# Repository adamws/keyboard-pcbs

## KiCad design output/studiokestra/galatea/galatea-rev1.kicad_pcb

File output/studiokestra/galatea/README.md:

## studiokestra/galatea/galatea-rev1

[layout](galatea-rev1-kle.json) - [PCB](galatea-rev1.kicad_pcb)

{:loading="lazy"}

[Open in keyboard-layout-editor](http://www.keyboard-layout-editor.com/##@@_x:2.5&y:1.25&c=#777777;&=0,0&_x:0.25&c=#cccccc;&=1,0%0A%0A%0A0,0&=0,1%0A%0A%0A0,0&=0,2%0A%0A%0A0,0&=1,2%0A%0A%0A0,0&_x:0.25&c=#aaaaaa;&=0,3%0A%0A%0A0,0&=1,3%0A%0A%0A0,0&=0,4%0A%0A%0A0,0&=1,4%0A%0A%0A0,0&_x:0.25&c=#cccccc;&=0,5%0A%0A%0A0,0&=1,5%0A%0A%0A0,0&=0,6%0A%0A%0A0,0&=1,6%0A%0A%0A0,0&_x:0.25&c=#aaaaaa;&=0,7%0A%0A%0A0,0&_x:0.25&c=#cccccc;&=1,7&=0,8&=1,8;&@_x:2.5&y:0.25&c=#aaaaaa;&=2,0&_c=#cccccc;&=3,0&=2,1&=3,1&=2,2&=3,2&=2,3&=3,3&=2,4&=3,4&=2,5&=3,5&=2,6&_c=#aaaaaa&w:2;&=3,6%0A%0A%0A1,0&_x:0.25&c=#cccccc;&=3,7&=2,8&=3,8;&@_x:2.5&c=#aaaaaa&w:1.5;&=4,0&_c=#cccccc;&=5,0&=4,1&=5,1&=4,2&=5,2&=4,3&=5,3&=4,4&=5,4&=4,5&=5,5&=4,6&_w:1.5;&=4,7%0A%0A%0A2,0&_x:0.25;&=5,7&=4,8&=5,8;&@_x:2.5&c=#aaaaaa&w:1.75;&=6,0&_c=#cccccc;&=7,0&=6,1&=7,1&=6,2&=7,2&=6,3&=7,3&=6,4&=7,4&=6,5&=7,5&_c=#777777&w:2.25;&=6,6%0A%0A%0A2,0;&@_x:2.5&c=#aaaaaa&w:2.25;&=8,0%0A%0A%0A3,0&_c=#cccccc;&=8,1&=9,1&=8,2&=9,2&=8,3&=9,3&=8,4&=9,4&=8,5&=9,5&_c=#aaaaaa&w:2.75;&=8,6%0A%0A%0A4,0&_x:1.25&c=#cccccc;&=8,8;&@_x:2.5&c=#aaaaaa&w:1.25;&=10,0%0A%0A%0A5,0&_w:1.25;&=11,0%0A%0A%0A5,0&_w:1.25;&=10,1%0A%0A%0A5,0&_c=#cccccc&w:6.25;&=10,3%0A%0A%0A5,0&_c=#aaaaaa&w:1.25;&=10,5%0A%0A%0A5,0&_w:1.25;&=11,5%0A%0A%0A5,0&_w:1.25;&=10,6%0A%0A%0A5,0&_w:1.25;&=10,7%0A%0A%0A5,0&_x:0.25&c=#cccccc;&=11,7&=10,8&=11,8;&@_x:3.75&y:-7.5&d:true;&=1,0%0A%0A%0A0,1&_x:-0.25;&=0,1%0A%0A%0A0,1&=0,2%0A%0A%0A0,1&=1,2%0A%0A%0A0,1&=0,3%0A%0A%0A0,1&_x:0.5&c=#aaaaaa;&=1,3%0A%0A%0A0,1&=0,4%0A%0A%0A0,1&=1,4%0A%0A%0A0,1&=0,5%0A%0A%0A0,1&_x:0.5&c=#cccccc;&=1,5%0A%0A%0A0,1&=0,6%0A%0A%0A0,1&=1,6%0A%0A%0A0,1&=0,7%0A%0A%0A0,1;&@_x:21.75&y:1.5;&=3,6%0A%0A%0A1,1&=2,7%0A%0A%0A1,1;&@_x:22.5&c=#777777&w:1.25&h:2&w2:1.5&h2:1&x2:-0.25;&=4,7%0A%0A%0A2,1;&@_x:21.5&c=#cccccc;&=6,6%0A%0A%0A2,1;&@_c=#aaaaaa&w:1.25;&=8,0%0A%0A%0A3,1&=9,0%0A%0A%0A3,1&_x:18.75&w:1.75;&=8,6%0A%0A%0A4,1&=8,7%0A%0A%0A4,1;&@_x:2.5&y:1.25&w:1.5;&=10,0%0A%0A%0A5,1&=11,0%0A%0A%0A5,1&_w:1.5;&=10,1%0A%0A%0A5,1&_c=#cccccc&w:7;&=10,3%0A%0A%0A5,1&_c=#aaaaaa&w:1.5;&=11,5%0A%0A%0A5,1&=10,6%0A%0A%0A5,1&_w:1.5;&=10,7%0A%0A%0A5,1;&@_x:2.5&w:1.5;&=10,0%0A%0A%0A5,2&_c=#cccccc&d:true;&=11,0%0A%0A%0A5,2&_c=#aaaaaa&w:1.5;&=10,1%0A%0A%0A5,2&_c=#cccccc&w:7;&=10,3%0A%0A%0A5,2&_c=#aaaaaa&w:1.5;&=11,5%0A%0A%0A5,2&_c=#cccccc&d:true;&=10,6%0A%0A%0A5,2&_c=#aaaaaa&w:1.5;&=10,7%0A%0A%0A5,2;&@_x:2.5&w:1.25;&=10,0%0A%0A%0A5,3&_w:1.25;&=11,0%0A%0A%0A5,3&_c=#cccccc&w:10;&=10,3%0A%0A%0A5,3&_c=#aaaaaa&w:1.25;&=10,6%0A%0A%0A5,3&_w:1.25;&=10,7%0A%0A%0A5,3;&@_x:2.5&w:1.5;&=10,0%0A%0A%0A5,4&_c=#cccccc&d:true;&=11,0%0A%0A%0A5,4&_w:10;&=10,3%0A%0A%0A5,4&_d:true;&=10,6%0A%0A%0A5,4&_c=#aaaaaa&w:1.5;&=10,7%0A%0A%0A5,4)

{:loading="lazy"}

## studiokestra/galatea/galatea-rev2

[layout](galatea-rev2-kle.json) - [PCB](galatea-rev2.kicad_pcb)

{:loading="lazy"}

[Open in keyboard-layout-editor](http://www.keyboard-layout-editor.com/##@@_x:2.5&y:1.25&c=#777777;&=0,0&_x:0.25&c=#cccccc;&=1,0%0A%0A%0A0,0&=0,1%0A%0A%0A0,0&=0,2%0A%0A%0A0,0&=1,2%0A%0A%0A0,0&_x:0.25&c=#aaaaaa;&=0,3%0A%0A%0A0,0&=1,3%0A%0A%0A0,0&=0,4%0A%0A%0A0,0&=1,4%0A%0A%0A0,0&_x:0.25&c=#cccccc;&=0,5%0A%0A%0A0,0&=1,5%0A%0A%0A0,0&=0,6%0A%0A%0A0,0&=1,6%0A%0A%0A0,0&_x:0.25&c=#aaaaaa;&=0,7%0A%0A%0A0,0&_x:0.25&c=#cccccc;&=1,7&=0,8&=1,8;&@_x:2.5&y:0.25&c=#aaaaaa;&=2,0&_c=#cccccc;&=3,0&=2,1&=3,1&=2,2&=3,2&=2,3&=3,3&=2,4&=3,4&=2,5&=3,5&=2,6&_c=#aaaaaa&w:2;&=3,6%0A%0A%0A1,0&_x:0.25&c=#cccccc;&=3,7&=2,8&=3,8;&@_x:2.5&c=#aaaaaa&w:1.5;&=4,0&_c=#cccccc;&=5,0&=4,1&=5,1&=4,2&=5,2&=4,3&=5,3&=4,4&=5,4&=4,5&=5,5&=4,6&_w:1.5;&=4,7%0A%0A%0A2,0&_x:0.25;&=5,7&=4,8&=5,8;&@_x:2.5&c=#aaaaaa&w:1.75;&=6,0&_c=#cccccc;&=7,0&=6,1&=7,1&=6,2&=7,2&=6,3&=7,3&=6,4&=7,4&=6,5&=7,5&_c=#777777&w:2.25;&=6,6%0A%0A%0A2,0;&@_x:2.5&c=#aaaaaa&w:2.25;&=8,0%0A%0A%0A3,0&_c=#cccccc;&=8,1&=9,1&=8,2&=9,2&=8,3&=9,3&=8,4&=9,4&=8,5&=9,5&_c=#aaaaaa&w:2.75;&=8,6%0A%0A%0A4,0&_x:1.25&c=#cccccc;&=8,8;&@_x:2.5&c=#aaaaaa&w:1.25;&=10,0%0A%0A%0A5,0&_w:1.25;&=11,0%0A%0A%0A5,0&_w:1.25;&=10,1%0A%0A%0A5,0&_c=#cccccc&w:6.25;&=10,3%0A%0A%0A5,0&_c=#aaaaaa&w:1.25;&=10,5%0A%0A%0A5,0&_w:1.25;&=11,5%0A%0A%0A5,0&_w:1.25;&=10,6%0A%0A%0A5,0&_w:1.25;&=10,7%0A%0A%0A5,0&_x:0.25&c=#cccccc;&=11,7&=10,8&=11,8;&@_x:3.75&y:-7.5&d:true;&=1,0%0A%0A%0A0,1&_x:-0.25;&=0,1%0A%0A%0A0,1&=0,2%0A%0A%0A0,1&=1,2%0A%0A%0A0,1&=0,3%0A%0A%0A0,1&_x:0.5&c=#aaaaaa;&=1,3%0A%0A%0A0,1&=0,4%0A%0A%0A0,1&=1,4%0A%0A%0A0,1&=0,5%0A%0A%0A0,1&_x:0.5&c=#cccccc;&=1,5%0A%0A%0A0,1&=0,6%0A%0A%0A0,1&=1,6%0A%0A%0A0,1&=0,7%0A%0A%0A0,1;&@_x:21.75&y:1.5;&=3,6%0A%0A%0A1,1&=2,7%0A%0A%0A1,1;&@_x:22.5&c=#777777&w:1.25&h:2&w2:1.5&h2:1&x2:-0.25;&=4,7%0A%0A%0A2,1;&@_x:21.5&c=#cccccc;&=6,6%0A%0A%0A2,1;&@_c=#aaaaaa&w:1.25;&=8,0%0A%0A%0A3,1&=9,0%0A%0A%0A3,1&_x:18.75&w:1.75;&=8,6%0A%0A%0A4,1&=8,7%0A%0A%0A4,1;&@_x:2.5&y:1.25&w:1.5;&=10,0%0A%0A%0A5,1&=11,0%0A%0A%0A5,1&_w:1.5;&=10,1%0A%0A%0A5,1&_c=#cccccc&w:7;&=10,3%0A%0A%0A5,1&_c=#aaaaaa&w:1.5;&=11,5%0A%0A%0A5,1&=10,6%0A%0A%0A5,1&_w:1.5;&=10,7%0A%0A%0A5,1;&@_x:2.5&w:1.5;&=10,0%0A%0A%0A5,2&_c=#cccccc&d:true;&=11,0%0A%0A%0A5,2&_c=#aaaaaa&w:1.5;&=10,1%0A%0A%0A5,2&_c=#cccccc&w:7;&=10,3%0A%0A%0A5,2&_c=#aaaaaa&w:1.5;&=11,5%0A%0A%0A5,2&_c=#cccccc&d:true;&=10,6%0A%0A%0A5,2&_c=#aaaaaa&w:1.5;&=10,7%0A%0A%0A5,2;&@_x:2.5&w:1.25;&=10,0%0A%0A%0A5,3&_w:1.25;&=11,0%0A%0A%0A5,3&_c=#cccccc&w:10;&=10,3%0A%0A%0A5,3&_c=#aaaaaa&w:1.25;&=10,6%0A%0A%0A5,3&_w:1.25;&=10,7%0A%0A%0A5,3;&@_x:2.5&w:1.5;&=10,0%0A%0A%0A5,4&_c=#cccccc&d:true;&=11,0%0A%0A%0A5,4&_w:10;&=10,3%0A%0A%0A5,4&_d:true;&=10,6%0A%0A%0A5,4&_c=#aaaaaa&w:1.5;&=10,7%0A%0A%0A5,4)

{:loading="lazy"}

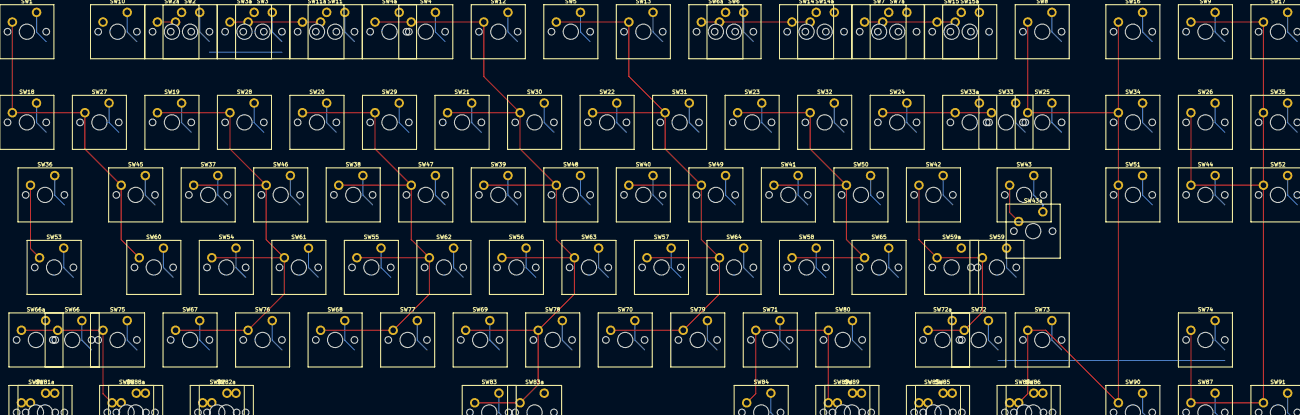
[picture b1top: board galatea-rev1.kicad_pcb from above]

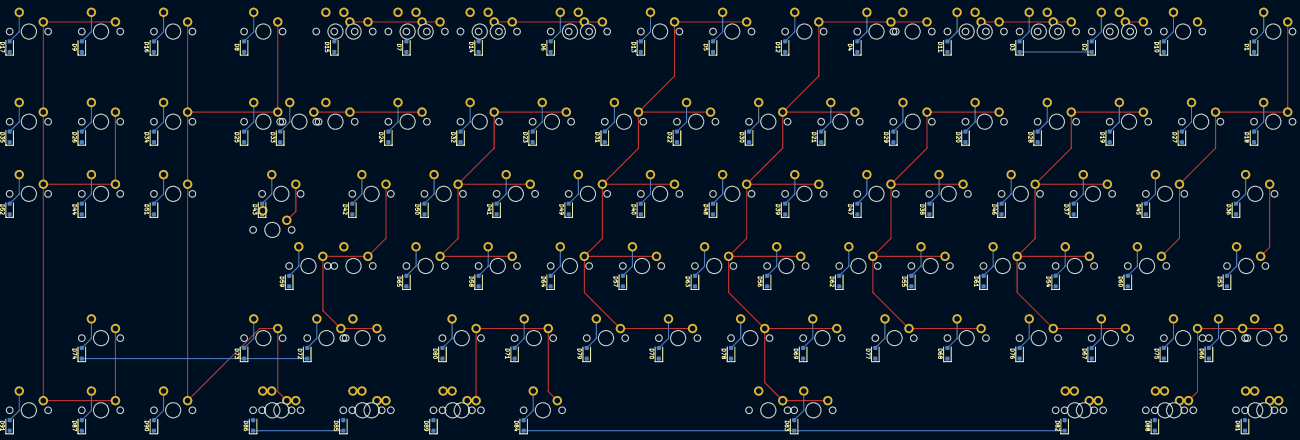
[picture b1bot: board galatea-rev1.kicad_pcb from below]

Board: 2 copper layers, 202 parts (91 on the bottom side), 112 nets.

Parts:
D1, D2, D3, D4, D5, D6, D7, D8, D9, D10, D11, D12, D13, D14, D15, D16, D17, D18, D19, D20, D21, D22, D23, D24, D25, D26, D27, D28, D29, D30, D31, D32, D33, D34, D35, D36, D37, D38, D39, D40, D41, D42, D43, D44, D45, D46, D47, D48, D49, D50, D51, D52, D53, D54, D55, D56, D57, D58, D59, D60, D61, D62, D63, D64, D65, D66, D67, D68, D69, D70, D71, D72, D73, D74, D75, D76, D77, D78, D79, D80, D81, D82, D83, D84, D85, D86, D87, D88, D89, D90, D91: D_SOD-123F
SW1, SW2, SW2a, SW3, SW3a, SW4, SW4a, SW5, SW6, SW6a, SW7, SW7a, SW8, SW9, SW10, SW11, SW11a, SW12, SW13, SW14, SW14a, SW15, SW15a, SW16, SW17, SW18, SW19, SW20, SW21, SW22, SW23, SW24, SW25, SW26, SW27, SW28, SW29, SW30, SW31, SW32, SW33, SW33a, SW34, SW35, SW36, SW37, SW38, SW39, SW40, SW41, SW42, SW43, SW43a, SW44, SW45, SW46, SW47, SW48, SW49, SW50, SW51, SW52, SW53, SW54, SW55, SW56, SW57, SW58, SW59, SW59a, SW60, SW61, SW62, SW63, SW64, SW65, SW66, SW66a, SW67, SW68, SW69, SW70, SW71, SW72, SW72a, SW73, SW74, SW75, SW76, SW77, SW78, SW79, SW80, SW81, SW81a, SW82, SW82a, SW83, SW83a, SW84, SW85, SW85a, SW86, SW86a, SW87, SW88, SW88a, SW89, SW89a, SW90, SW91: SW_Cherry_MX_PCB_1.00u

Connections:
COL0: SW1.1, SW10.1, SW18.1, SW27.1, SW36.1, SW45.1, SW53.1, SW60.1, SW66.1, SW66a.1, SW75.1, SW81.1, SW81a.1, SW88.1, SW88a.1
COL1: SW2.1, SW2a.1, SW19.1, SW28.1, SW37.1, SW46.1, SW54.1, SW61.1, SW67.1, SW76.1, SW82.1, SW82a.1
COL2: SW3.1, SW3a.1, SW11.1, SW11a.1, SW20.1, SW29.1, SW38.1, SW47.1, SW55.1, SW62.1, SW68.1, SW77.1
COL3: SW4.1, SW4a.1, SW12.1, SW21.1, SW30.1, SW39.1, SW48.1, SW56.1, SW63.1, SW69.1, SW78.1, SW83.1, SW83a.1
COL4: SW5.1, SW13.1, SW22.1, SW31.1, SW40.1, SW49.1, SW57.1, SW64.1, SW70.1, SW79.1
COL5: SW6.1, SW6a.1, SW14.1, SW14a.1, SW23.1, SW32.1, SW41.1, SW50.1, SW58.1, SW65.1, SW71.1, SW80.1, SW84.1, SW89.1, SW89a.1
COL6: SW7.1, SW7a.1, SW15.1, SW15a.1, SW24.1, SW33.1, SW33a.1, SW42.1, SW59.1, SW59a.1, SW72.1, SW72a.1, SW85.1, SW85a.1
COL7: SW8.1, SW16.1, SW25.1, SW34.1, SW43.1, SW43a.1, SW51.1, SW73.1, SW86.1, SW86a.1, SW90.1
COL8: SW9.1, SW17.1, SW26.1, SW35.1, SW44.1, SW52.1, SW74.1, SW87.1, SW91.1
unnamed: D1.2, SW1.2
unnamed: D2.2, SW2.2, SW2a.2
unnamed: D3.2, SW3.2, SW3a.2
unnamed: D4.2, SW4.2, SW4a.2
unnamed: D5.2, SW5.2
unnamed: D6.2, SW6.2, SW6a.2
unnamed: D7.2, SW7.2, SW7a.2
unnamed: D8.2, SW8.2
unnamed: D9.2, SW9.2
unnamed: D10.2, SW10.2
unnamed: D11.2, SW11.2, SW11a.2
unnamed: D12.2, SW12.2
unnamed: D13.2, SW13.2
unnamed: D14.2, SW14.2, SW14a.2
unnamed: D15.2, SW15.2, SW15a.2
unnamed: D16.2, SW16.2
unnamed: D17.2, SW17.2
unnamed: D18.2, SW18.2
unnamed: D19.2, SW19.2
unnamed: D20.2, SW20.2
unnamed: D21.2, SW21.2
unnamed: D22.2, SW22.2
unnamed: D23.2, SW23.2
unnamed: D24.2, SW24.2
unnamed: D25.2, SW25.2
unnamed: D26.2, SW26.2
unnamed: D27.2, SW27.2
unnamed: D28.2, SW28.2
unnamed: D29.2, SW29.2
unnamed: D30.2, SW30.2
unnamed: D31.2, SW31.2
unnamed: D32.2, SW32.2
unnamed: D33.2, SW33.2, SW33a.2
unnamed: D34.2, SW34.2
unnamed: D35.2, SW35.2
unnamed: D36.2, SW36.2
unnamed: D37.2, SW37.2
unnamed: D38.2, SW38.2
unnamed: D39.2, SW39.2
unnamed: D40.2, SW40.2
unnamed: D41.2, SW41.2
unnamed: D42.2, SW42.2
unnamed: D43.2, SW43.2, SW43a.2
unnamed: D44.2, SW44.2
unnamed: D45.2, SW45.2
unnamed: D46.2, SW46.2
unnamed: D47.2, SW47.2
unnamed: D48.2, SW48.2
unnamed: D49.2, SW49.2
unnamed: D50.2, SW50.2
unnamed: D51.2, SW51.2
unnamed: D52.2, SW52.2
unnamed: D53.2, SW53.2
unnamed: D54.2, SW54.2
unnamed: D55.2, SW55.2
unnamed: D56.2, SW56.2
unnamed: D57.2, SW57.2
unnamed: D58.2, SW58.2
unnamed: D59.2, SW59.2, SW59a.2
unnamed: D60.2, SW60.2
unnamed: D61.2, SW61.2
unnamed: D62.2, SW62.2
unnamed: D63.2, SW63.2
unnamed: D64.2, SW64.2
unnamed: D65.2, SW65.2
unnamed: D66.2, SW66.2, SW66a.2
unnamed: D67.2, SW67.2
unnamed: D68.2, SW68.2
unnamed: D69.2, SW69.2
unnamed: D70.2, SW70.2
unnamed: D71.2, SW71.2
unnamed: D72.2, SW72.2, SW72a.2
unnamed: D73.2, SW73.2
unnamed: D74.2, SW74.2
unnamed: D75.2, SW75.2
unnamed: D76.2, SW76.2
unnamed: D77.2, SW77.2
unnamed: D78.2, SW78.2
unnamed: D79.2, SW79.2
unnamed: D80.2, SW80.2
unnamed: D81.2, SW81.2, SW81a.2
unnamed: D82.2, SW82.2, SW82a.2
unnamed: D83.2, SW83.2, SW83a.2
unnamed: D84.2, SW84.2
unnamed: D85.2, SW85.2, SW85a.2
unnamed: D86.2, SW86.2, SW86a.2
unnamed: D87.2, SW87.2
unnamed: D88.2, SW88.2, SW88a.2
unnamed: D89.2, SW89.2, SW89a.2
unnamed: D90.2, SW90.2
unnamed: D91.2, SW91.2
ROW0: D1.1, D2.1, D3.1, D4.1, D5.1, D6.1, D7.1, D8.1, D9.1
ROW1: D10.1, D11.1, D12.1, D13.1, D14.1, D15.1, D16.1, D17.1
ROW2: D18.1, D19.1, D20.1, D21.1, D22.1, D23.1, D24.1, D25.1, D26.1
ROW3: D27.1, D28.1, D29.1, D30.1, D31.1, D32.1, D33.1, D34.1, D35.1
ROW4: D36.1, D37.1, D38.1, D39.1, D40.1, D41.1, D42.1, D43.1, D44.1
ROW5: D45.1, D46.1, D47.1, D48.1, D49.1, D50.1, D51.1, D52.1
ROW6: D53.1, D54.1, D55.1, D56.1, D57.1, D58.1, D59.1
ROW7: D60.1, D61.1, D62.1, D63.1, D64.1, D65.1
ROW8: D66.1, D67.1, D68.1, D69.1, D70.1, D71.1, D72.1, D73.1, D74.1
ROW9: D75.1, D76.1, D77.1, D78.1, D79.1, D80.1
ROW10: D81.1, D82.1, D83.1, D84.1, D85.1, D86.1, D87.1
ROW11: D88.1, D89.1, D90.1, D91.1

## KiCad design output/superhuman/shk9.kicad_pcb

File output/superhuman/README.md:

## superhuman/shk9

[layout](shk9-kle.json) - [PCB](shk9.kicad_pcb)

{:loading="lazy"}

[Open in keyboard-layout-editor](http://www.keyboard-layout-editor.com/##@@=0,0&=0,1&=0,2;&@=1,0&=1,1&=1,2;&@=2,0&=2,1&=2,2)

{:loading="lazy"}

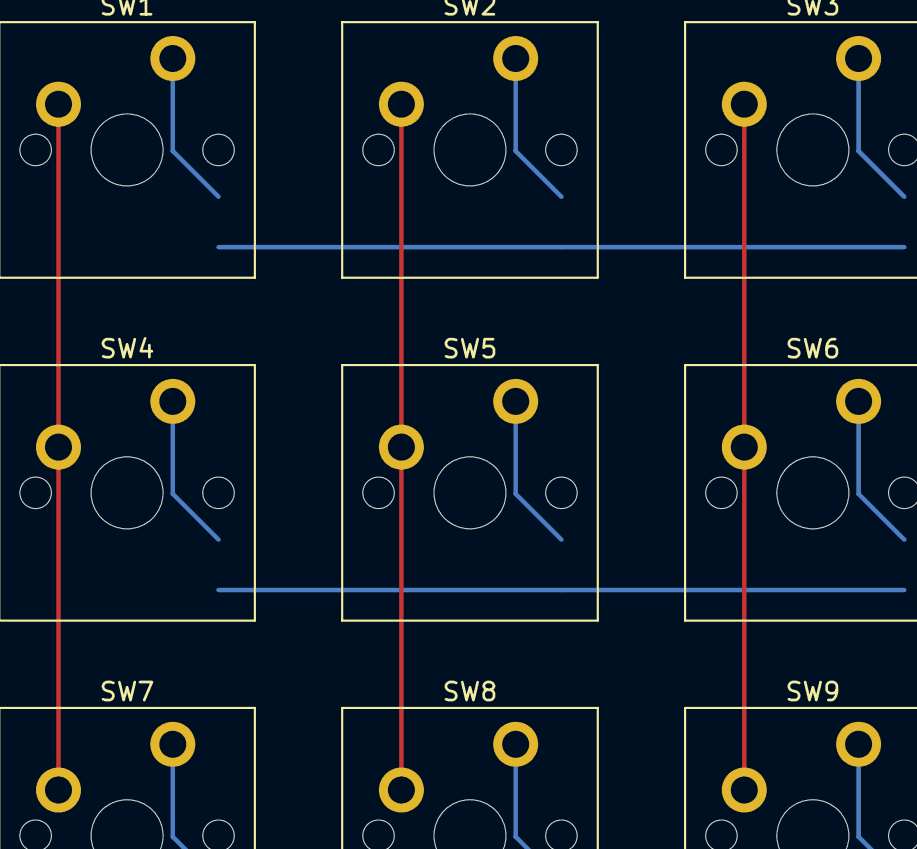
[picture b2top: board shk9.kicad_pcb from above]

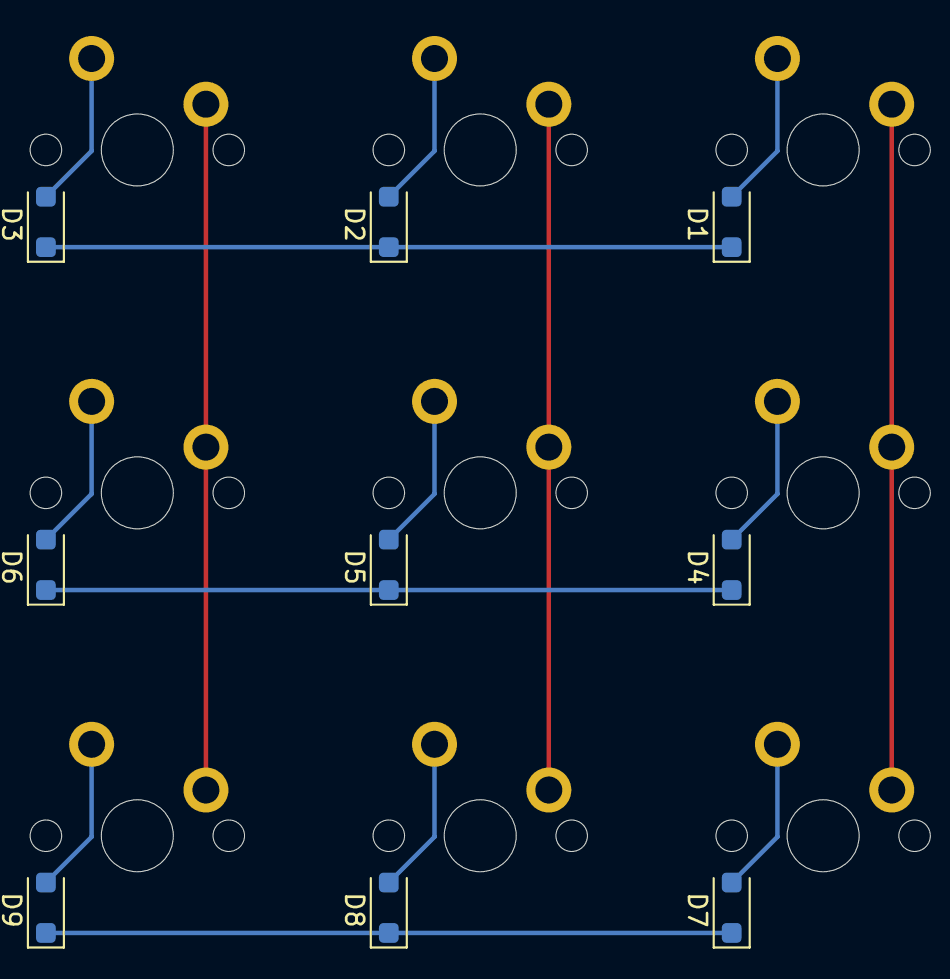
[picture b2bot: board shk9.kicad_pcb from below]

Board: 2 copper layers, 18 parts (9 on the bottom side), 15 nets.

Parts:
D1, D2, D3, D4, D5, D6, D7, D8, D9: D_SOD-123F
SW1, SW2, SW3, SW4, SW5, SW6, SW7, SW8, SW9: SW_Cherry_MX_PCB_1.00u

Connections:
COL0: SW1.1, SW4.1, SW7.1
COL1: SW2.1, SW5.1, SW8.1
COL2: SW3.1, SW6.1, SW9.1
unnamed: D1.2, SW1.2
unnamed: D2.2, SW2.2
unnamed: D3.2, SW3.2
unnamed: D4.2, SW4.2
unnamed: D5.2, SW5.2
unnamed: D6.2, SW6.2
unnamed: D7.2, SW7.2
unnamed: D8.2, SW8.2
unnamed: D9.2, SW9.2
ROW0: D1.1, D2.1, D3.1
ROW1: D4.1, D5.1, D6.1
ROW2: D7.1, D8.1, D9.1
